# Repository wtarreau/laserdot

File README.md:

laserdot
========

A small program running in a microcontroller to place between a laser engraver
controller and the laser module to always turn the laser on at a very low duty
cycle, permitting to see the dot to adjust the focus, position and alignment.

Just build it using "make MCU=" with the microcontroller name (attiny85 and
attiny13 are currently supported, others may be trivially added).

It has no dependency beyond an AVR toolchain like the one provided with any
Arduino IDE. The program can also trivially be imported as an Arduino project
for those more familiar with this heavier approach.

A circuit is provided, made of a schematic and a board, for those who want to
quickly implement it. It's made around an ATTINY13A which is as cheap as a
555 these days. The output uses 4 pins at 2.0 pitch to match my NEJE-20W laser
module, and the input uses a male JST-XH 2.54mm connector to match the
connector at the end of the cable on the laser module side. It's worth noting
that the cable is not straight but reversed, so the polarity here really
requires the cable or needs to be reversed.

The micro-controller may be programmed in situ using an SOP8 clamp provided
the module is disconnected from both sides. Indeed, no pin prevents this from
being done since there are no local component connections. I'm also using this
to program a different duty cycle in its EEPROM, like here, 0.2% duty cycle :

```
$ avrdude -c buspirate -P /dev/ttyUSB0 -p attiny13 -U eeprom:w:0x02:m
```

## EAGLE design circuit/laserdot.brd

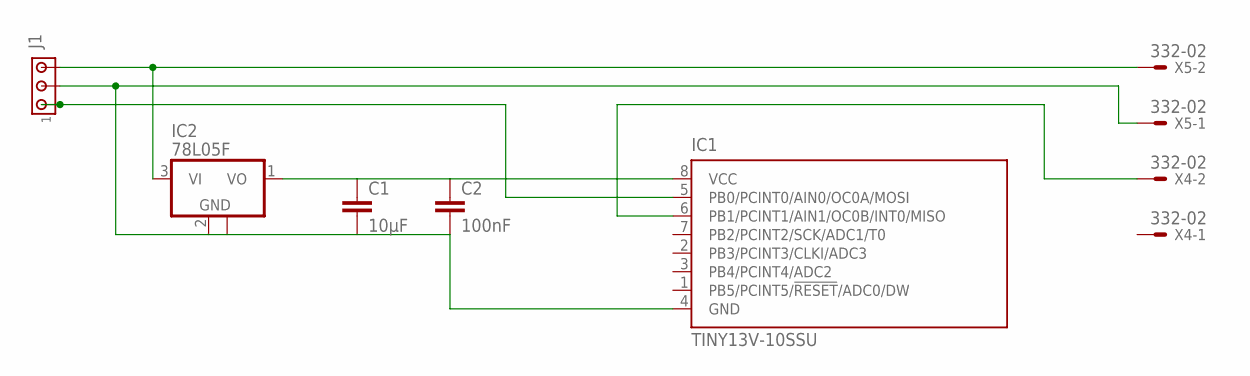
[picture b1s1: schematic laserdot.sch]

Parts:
C1: 10µF; C0805
C2: 100nF; C0805
IC1: TINY13V-10SSU; 8S1
IC2: 78L05F; SOT89
J1: MTA03-100; 10X03MTA
X4, X5: 332-02

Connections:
unnamed: IC2.3 (VI), J1.3, X5.2
unnamed: C1.2, C2.2, IC1.4 (GND), IC2.2 (GND), IC2.2@1 (GND), J1.2, X5.1
unnamed: IC1.5 (PB0/PCINT0/AIN0/OC0A/MOSI), J1.1
unnamed: C1.1, C2.1, IC1.8 (VCC), IC2.1 (VO)
unnamed: IC1.6 (PB1/PCINT1/AIN1/OC0B/INT0/MISO), X4.2

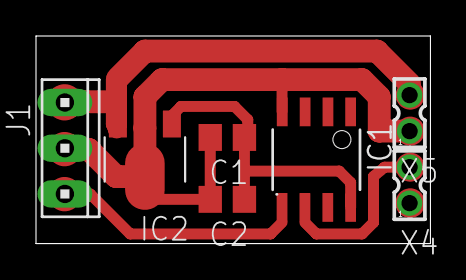
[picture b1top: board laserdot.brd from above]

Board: 2 copper layers, 21.9 x 11.5 mm, 7 parts (0 on the bottom side), 5 nets.

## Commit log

2019-09-20 code: create the first working version of the program
    The program retrieves the minimum duty cycle to use from the first
    eeprom's address and falls back to 0.5% if unset. It supports the
    TINY versions of AVR devices, with input on PB0 and output on PB1.
    It simply copies the input to the output and sends small pulses
    when the input is idle for too long. With high a enough clock it
    doesn't introduce any measurable latency effect, as the signal
2019-09-20 build: add a Makefile
    It supports attiny85 and attiny13 (to be set using MCU=) and can
    directly flash the device (make upload). The programmer defaults
    to a bus pirate, but it can also work with other ones like usbasp
    or usbtiny if needed.
2019-09-20 firmware: add pre-built firmwares for attiny13 and attiny85
    These ones just have to be flashed without requiring the build environment.
2019-09-20 circuit: add the laserdot schematic and board
    These ones are really trivial since there are only 4 components but they can
    save time to those willing to reimplement the circuit. The output uses 4 pin
    at 2.0 pitch to match my NEJE-20W laser, and the input uses a male JST-XH
    2.54mm connector to match the connector at the end of the cable on the laser
    module side. It's worth noting that the cable is not straight but reversed,
    so the polarity here really requires the cable or needs to be reversed.
2019-09-20 doc: add a readme
2022-07-31 doc: commit the photo of the finished module and add it to the README
    The photo of the finished module was never committed. Let's do it.
